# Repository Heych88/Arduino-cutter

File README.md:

# Arduino-cutter
Arduino controller implementation of a plastic or resistor cutter.

The controller daughter board contains the follow external board connections;

 * 6 -> 14v
 * Four push-buttons
 * Adjustable potentiometer
 * E-stops
 * 4-bit LCD
 * Single pulse encoder
 * Two solenoid relays, active low, 5v or Vin
 * Stepper motor, 2A
 * Fuse connector

## Hardware Setup

The parts required and the daughterboard PCB Gerber files are located in the EagleBoard folder.

The interfacing of the components is as follows.

## Installing

1. Clone this repository

 ```sh
 git clone https://github.com/Heych88/Arduino-cutter.git
 ```

2. Download Arduino IDE from [here](https://www.arduino.cc/en/Main/Software).

3. If you are installing a brand-new Arduino Leonardo board, the EEPROM must be flashed first. If it is the existing system board, continue from step 4.

 1. Load the `eeprom_write.ino` file, located in the `/src/eeprom_write/` folders, into the Arduino IDE.

 2. Compile and load the file onto the Arduino board.

4. Load any of the `.ino` files, located in the `/src/` folders, into the Arduino IDE.

5. Compile and load the files onto the Arduino board.

Detailed programming and system information can be found in the *Arduino Cutter Instructions* document, located in the `/documents/` folder.

## Usage

This repository provides a daughterboard and usable code to run an Arduino plastic or resistor cutter.

## Contributing

1. Fork it!
2. Create your feature branch: `git checkout -b my-new-feature`
3. Commit your changes: `git commit -am 'Add some feature'`
4. Push to the branch: `git push origin my-new-feature`
5. Submit a pull request :D

## License

This project is licensed under the GNU-GPL3 License - see the [LICENSE.md](LICENSE.md) file for details.

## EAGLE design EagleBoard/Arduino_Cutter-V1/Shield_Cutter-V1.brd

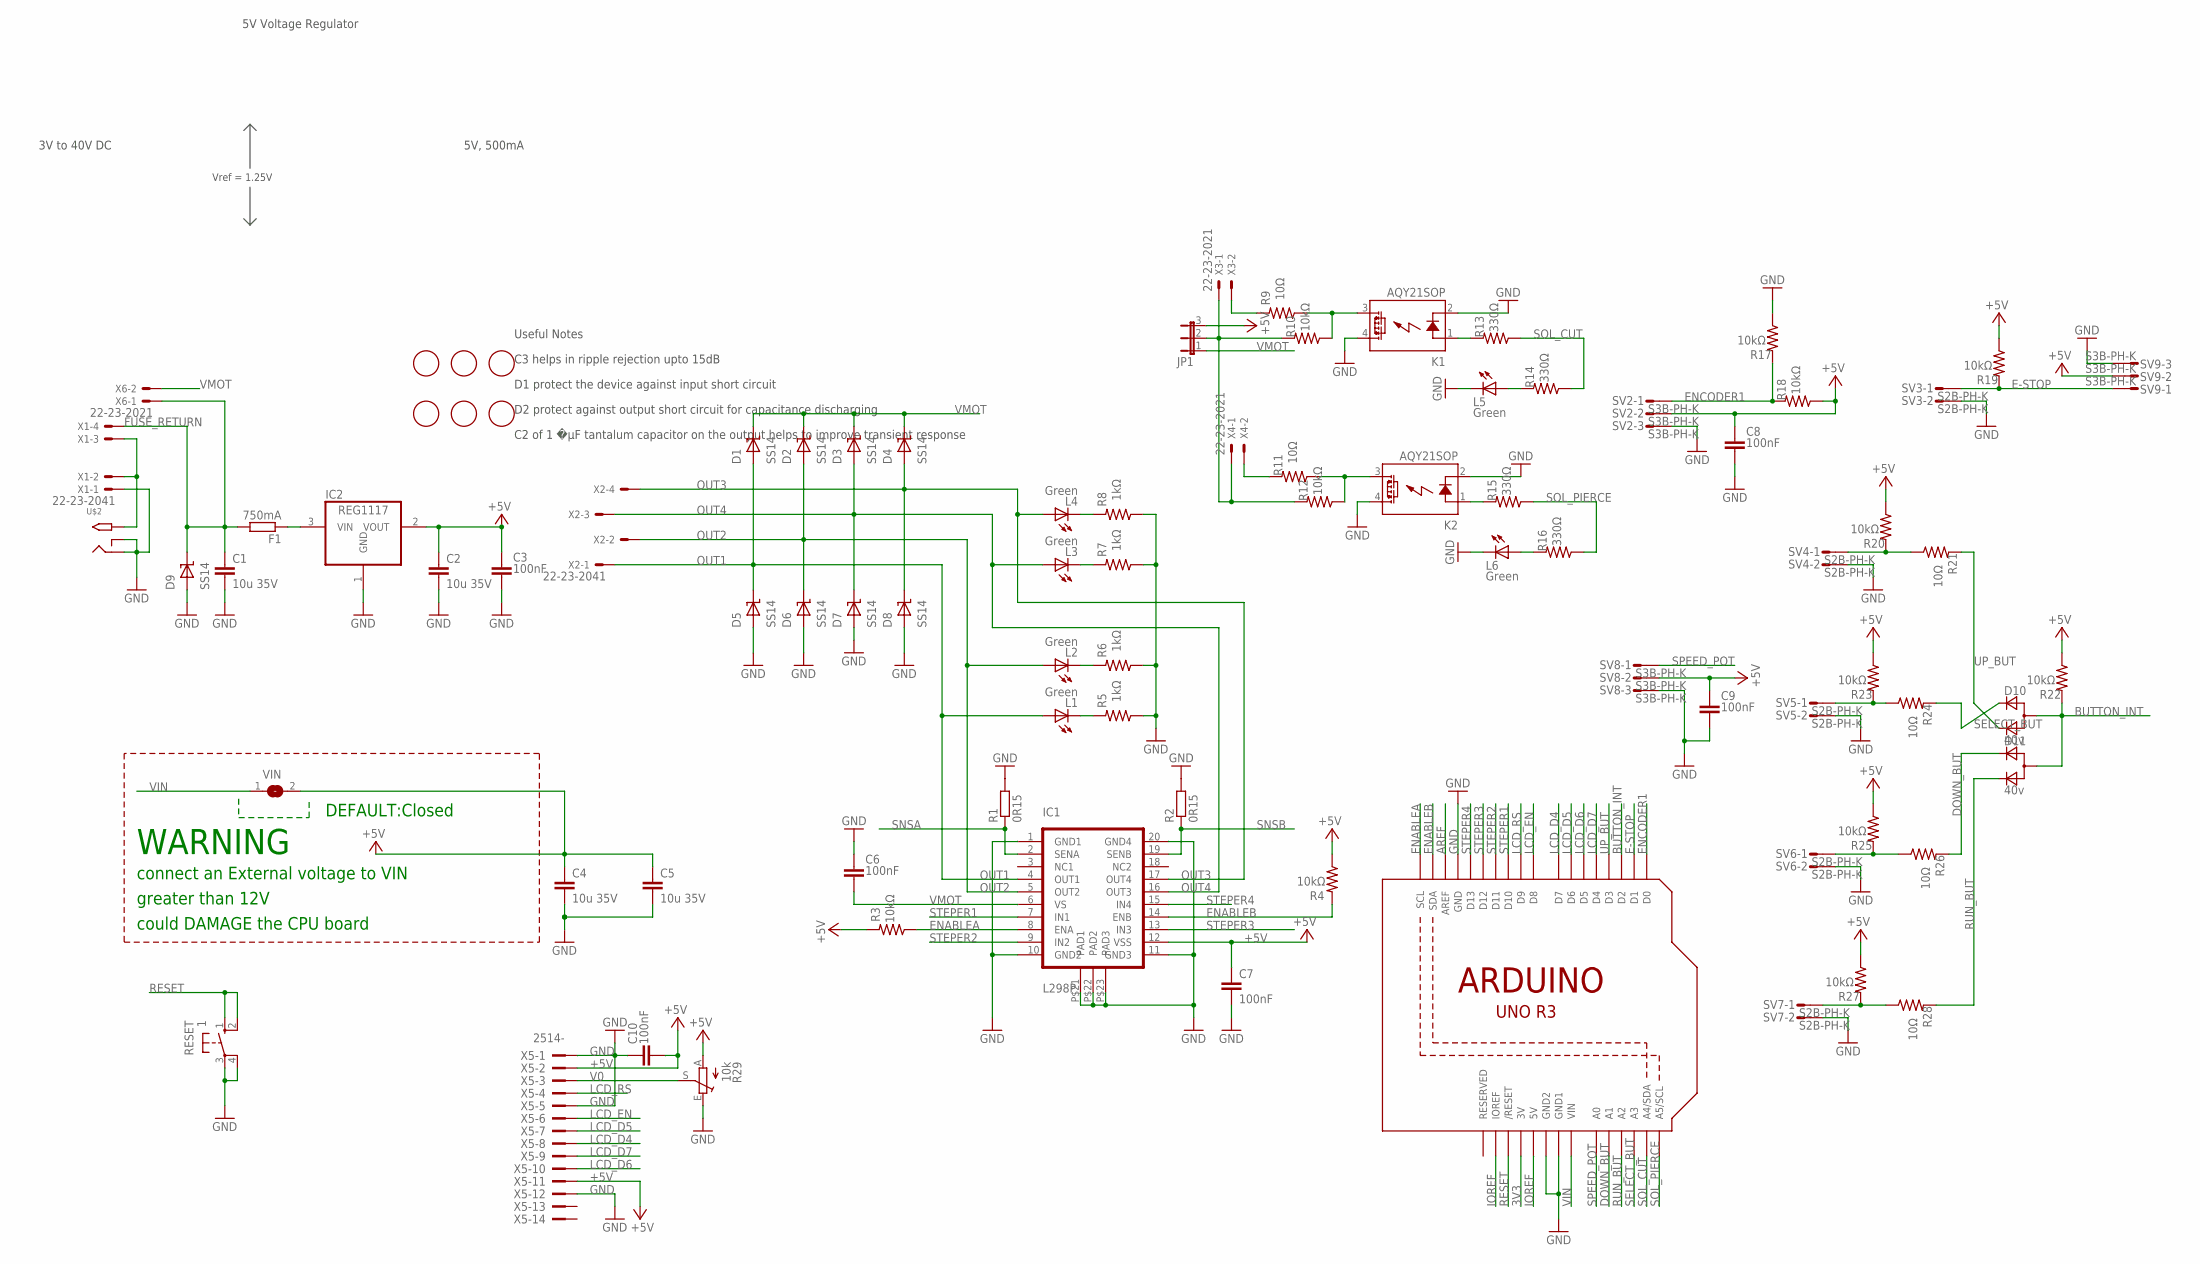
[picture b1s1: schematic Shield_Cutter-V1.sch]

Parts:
C1, C2, C4, C5: 10u 35V; C1210
C3, C6, C7, C8, C9, C10: 100nF; C0805
D1, D2, D3, D4, D5, D6, D7, D8, D9: SS14; SMA
D10, D11: 40v; SOT323
F1: 750mA; R1206
FID1, FID2, FID3, FID4, FID5, FID6: FIDUCIALMOUNT; FIDUCIA-MOUNT
IC1: L298P; POWER-SO20
IC2: REG1117; SOT223
JP1: JP2E; JP2
K1, K2: AQY21SOP; SOP04
L1, L2, L3, L4, L5, L6: Green; CHIPLED_0805
R1, R2: 0R15; R1206
R3, R4, R10, R12, R17, R18, R19, R20, R23, R25, R27: 10kΩ; R0805
R5, R6, R7, R8: 1kΩ; R0805
R9, R11, R21, R24, R26, R28: 10Ω; R0805
R13, R14, R15, R16: 330Ω; R0805
R22: 10kΩ; M0805
R29: 10k; S64W
RESET: 1; B3F-10XX
SV2, SV8, SV9: S3B-PH-K; S03P
SV3, SV4, SV5, SV6, SV7: S2B-PH-K; S02P
U1: ARDUINOR3-DIMENSION; ARDUINOR3
U$2: 2.1MMJACKTHM; PJ-102A
VIN: SJW
X1, X2: 22-23-2041
X3, X4, X6: 22-23-2021
X5: 2514-; PAK100/2500-14

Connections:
3V3: U1.3V
+5V: C2.1, C3.1, C4.1, C5.1, C7.1, C8.1, C9.1, C10.2, IC1.P$12 (VSS), IC2.2 (VOUT), JP1.3, R3.2, R4.1, R18.1, R19.1, R20.1, R22.1, R23.1, R25.1, R27.1, R29.A, SV2.2, SV8.2, SV9.2, VIN.2, X5.2, X5.11
AREF: U1.AREF
BUTTON_INT: D10.1 (A), D11.1 (A), R22.2, U1.D2
DOWN_BUT: D11.2 (C1), R26.2, U1.A1
E-STOP: R19.2, SV3.1, SV9.1, U1.D1
ENABLEA: IC1.P$8 (ENA), R3.1, U1.SCL
ENABLEB: IC1.P$14 (ENB), R4.2, U1.SDA
ENCODER1: R17.2, R18.2, SV2.1, U1.D0
FUSE_RETURN: C1.1, D9.P$1 (K), F1.2, X1.4, X6.1
GND: C1.2, C2.2, C3.2, C4.2, C5.2, C6.1, C7.2, C8.2, C9.2, C10.1, D5.P$2 (A), D6.P$2 (A), D7.P$2 (A), D8.P$2 (A), D9.P$2 (A), IC1.P$1 (GND1), IC1.P$10 (GND2), IC1.P$11 (GND3), IC1.P$20 (GND4), IC1.P$21 (PAD1), IC1.P$22 (PAD2), IC1.P$23 (PAD3), IC2.1 (GND), K1.2 (K), K1.4 (DS1), K2.2 (K), K2.4 (DS1), L5.C, L6.C, R1.2, R2.2, R5.1, R6.1, R7.1, R8.1, R17.1, R29.E, RESET.3, RESET.4 (P1), SV2.3, SV3.2, SV4.2, SV5.2, SV6.2, SV7.2, SV8.3, SV9.3, U1.GND, U1.GND1, U1.GND2, U$2.RING, U$2.RING_SW, X1.1, X5.1, X5.5, X5.12
IOREF: U1.5V, U1.IOREF
LCD_D4: U1.D7, X5.8
LCD_D5: U1.D6, X5.7
LCD_D6: U1.D5, X5.10
LCD_D7: U1.D4, X5.9
LCD_EN: U1.D8, X5.6
LCD_RS: U1.D9, X5.4
unnamed: L4.C, R8.2
unnamed: L3.C, R7.2
unnamed: L2.C, R6.2
unnamed: L1.C, R5.2
unnamed: K1.1 (A), R13.2
unnamed: L5.A, R14.2
unnamed: R9.2, X3.2
unnamed: R23.2, R24.1, SV5.1
unnamed: JP1.2, R10.2, R12.2, X3.1, X4.1
unnamed: K2.3 (DS2), R11.1, R12.1
unnamed: L6.A, R16.2
unnamed: R20.2, R21.1, SV4.1
unnamed: K2.1 (A), R15.2
unnamed: R11.2, X4.2
unnamed: K1.3 (DS2), R9.1, R10.1
unnamed: R25.2, R26.1, SV6.1
unnamed: F1.1, IC2.3 (VIN)
unnamed: R27.2, R28.1, SV7.1
OUT1: D1.P$2 (A), D5.P$1 (K), IC1.P$4 (OUT1), L1.A, X2.1
OUT2: D2.P$2 (A), D6.P$1 (K), IC1.P$5 (OUT2), L2.A, X2.2
OUT3: D4.P$2 (A), D8.P$1 (K), IC1.P$17 (OUT4), L4.A, X2.4
OUT4: D3.P$2 (A), D7.P$1 (K), IC1.P$16 (OUT3), L3.A, X2.3
POWERIN: U$2.TIP, X1.2, X1.3
RESET: RESET.1 (S), RESET.2 (S1), U1.RESET (/RESET)
RUN_BUT: D11.3 (C2), R28.2, U1.A2
SELECT_BUT: D10.2 (C1), R24.2, U1.A3
SNSA: IC1.P$2 (SENA), R1.1
SNSB: IC1.P$19 (SENB), R2.1
SOL_CUT: R13.1, R14.1, U1.A4 (A4/SDA)
SOL_PIERCE: R15.1, R16.1, U1.A5 (A5/SCL)
SPEED_POT: SV8.1, U1.A0
STEPER1: IC1.P$7 (IN1), U1.D10
STEPER2: IC1.P$9 (IN2), U1.D11
STEPER3: IC1.P$13 (IN3), U1.D12
STEPER4: IC1.P$15 (IN4), U1.D13
UP_BUT: D10.3 (C2), R21.2, U1.D3
V0: R29.S, X5.3
VIN: U1.VIN, VIN.1
VMOT: C6.2, D1.P$1 (K), D2.P$1 (K), D3.P$1 (K), D4.P$1 (K), IC1.P$6 (VS), JP1.1, X6.2

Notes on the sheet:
WARNING
connect an External voltage to VIN
greater than 12V
could DAMAGE the CPU board
DEFAULT:Closed
5V Voltage Regulator
C3 helps in ripple rejection upto 15dB
D1 protect the device against input short circuit
D2 protect against output short circuit for capacitance discharging
C2 of 1 �µF tantalum capacitor on the output helps to improve transient response
Useful Notes
5V, 500mA
3V to 40V DC
Vref = 1.25V

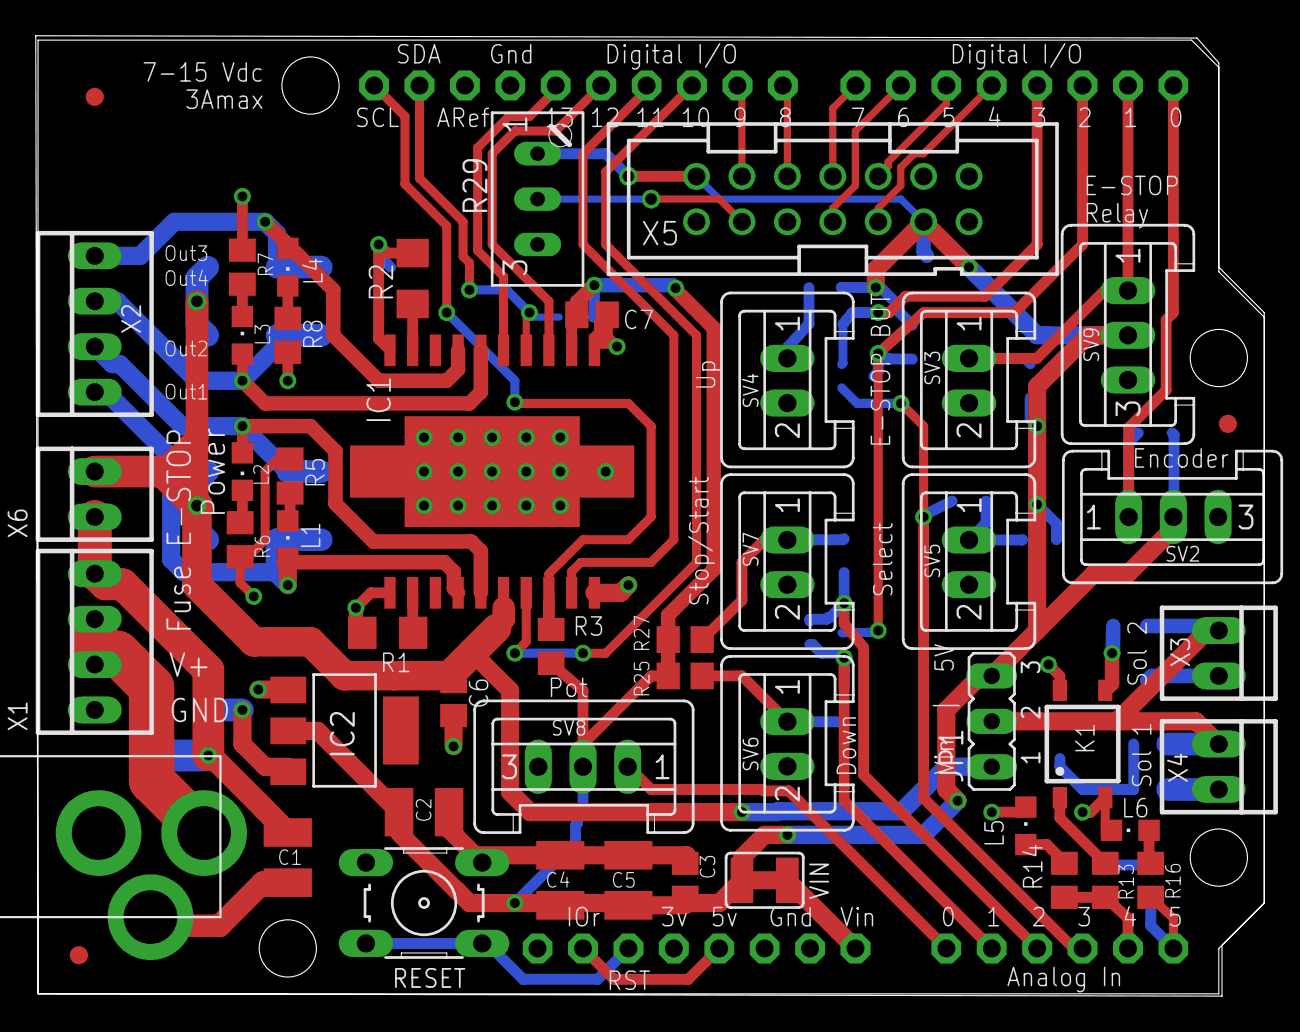
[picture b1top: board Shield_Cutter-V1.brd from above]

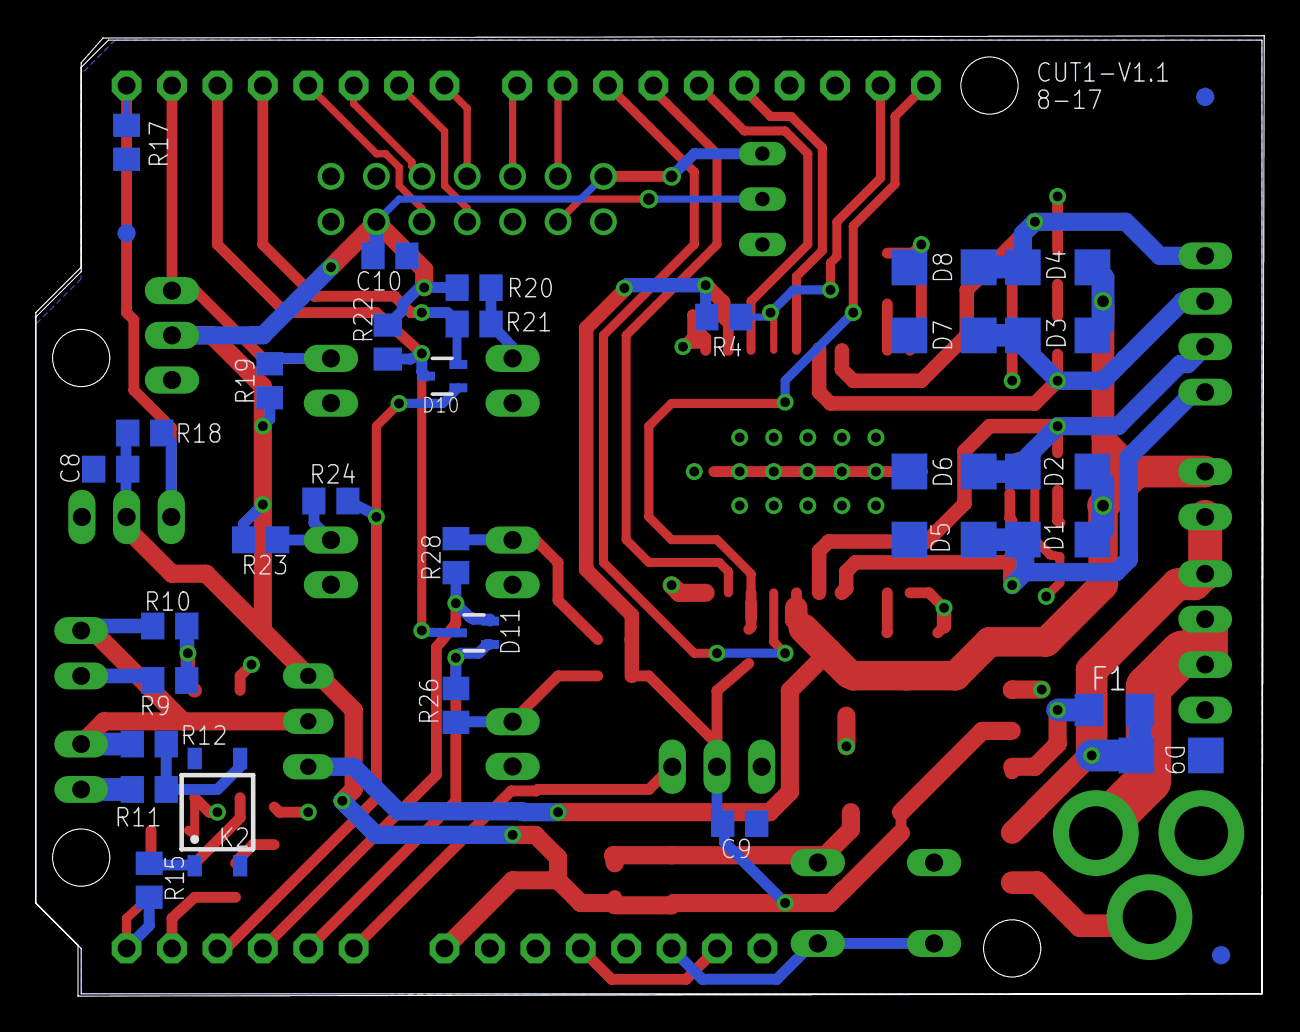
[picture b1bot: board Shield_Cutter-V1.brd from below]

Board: 2 copper layers, 68.7 x 53.7 mm, 86 parts (35 on the bottom side), 55 nets.

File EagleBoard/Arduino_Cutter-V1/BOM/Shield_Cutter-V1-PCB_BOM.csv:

Qty,Value,MPN,Digi-key,Package,Parts,Description
1,,61300311121,732-5316-ND,JP2,JP1,CONN HEADER 3 POS 2.54
2,0R15,RL1206FR-7W0R15L,311-.15LYCT-ND,R1206,"R1, R2",RES SMD 0.15 OHM 1% 1/2W 1206
1,,B3F-1002,SW401-ND,B3F-10XX,RESET,SWITCH TACTILE SPST-NO 0.05A 24V
6,100nF,C0805C104K5RACTU,399-1170-1-ND,C0805,"C3, C6, C7, C8, C9, C10",0.1µF ±10% 50V Ceramic Capacitor X7R 0805 (2012 Metric)
1,10k,PV36W103C01B00,490-2875-ND,S64W,R29,POTENTIOMETER
12,10kΩ,RMCF0805FT10K0,RMCF0805FT10K0CT-ND,R0805,"R3, R4, R10, R12, R17, R18, R19, R20, R22, R23, R25, R27","±1% 0.125W, 1/8W Chip Resistor 0805 (2012 Metric) "
4,10u 35V,C1210C106K3RACTU,399-8224-1-ND,C1210,"C1, C2, C4, C5","CAPACITOR, European symbol"
6,10Ω,RC0805FR-0710RL,RMCF0805FT10R0CT-ND,R0805,"R9, R11, R21, R24, R26, R28",RES SMD 10 OHM 1% 1/8W 0805
4,1kΩ,RMCF0805FT1K00,RMCF0805FT1K00CT-ND,R0805,"R5, R6, R7, R8","±1% 0.125W, 1/8W Chip Resistor 0805 (2012 Metric)"
3,22-23-2021,OSTVN02A150,ED10561-ND,22-23-2021,"X1, X4, X5",".100"" (2.54mm) Center Header - 2 Pin"
1,22-23-2041,OSTVN04A150,ED10563-ND,22-23-2041,X2,CONN TERM BLOCK 2.54MM 4POS PCB
1,2514-,302-S141,ED10522-ND,PAK100/2500-14,X5,"14 Positions Header Connector 0.100"" (2.54mm) Through Hole"
4,330Ω,RMCF0805FT330R,RMCF0805FT330RCT-ND,R0805,"R13, R14, R15, R16","±1% 0.125W, 1/8W Chip Resistor 0805 (2012 Metric)"
2,40v,"BAT54AW,115",1727-3567-1-ND,SOT323,"D10, D11","Diode Array 1 Pair Common Anode Schottky 200mA (DC) Surface Mount SC-70, SOT-323"
2,AQY21SOP,CPC1020NTR,CLA318CT-ND,SOP04,"K1, K2",PhotoMOS Relay NAiS
6,Green,LG R971-KN-1,475-1410-1-ND,CHIPLED_0805,"L1, L2, L3, L4, L5, L6",LED GREEN DIFFUSED 0805 SMD
1,L298P,L298P,497-1396-5-ND,POWER-SO20,IC1,L298P DUAL FUL-BRIDGE DRIVER PowerSO20
1,REG1117,REG1117-5/2K5,296-27924-1-ND,SOT223,IC2,800mA and 1A Low Dropout (LDO) Positive Regulator
6,S2B-PH-K,B2B-XH-A(LF)(SN),455-2247-ND,S02P,"SV1, SV3, SV4, SV5, SV6, SV7",CONN HEADER XH TOP 2POS 2.5MM
3,S3B-PH-K,B3B-XH-A(LF)(SN),455-2248-ND,S03P,"SV2, SV8, SV9",CONN HEADER XH TOP 3POS 2.5MM
9,SS14,MBRAF360T3G,MBRAF360T3GOSCT-ND,SMA,"D1, D2, D3, D4, D5, D6, D7, D8, D9",DIODE SCHOTTKY 60V 4A SMA

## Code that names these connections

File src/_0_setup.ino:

#include <LiquidCrystal.h>
#include <Stepper.h>

/******************************** Push Buttons & E-Stop *******************************/
#define E_STOP_BUT 1
#define BUTTON_INTERRUPT 2
#define SELECT_BUT A3
#define UP_BUT 3
#define DOWN_BUT A1
#define START_BUT A2

volatile bool e_stop_active = false;

/*************************************** LCD *****************************************/
// initialize the library with the numbers of the interface pins
LiquidCrystal lcd(9,8,6,7,4,5);

#define DISPLAY_ROWS 2
#define DISPLAY_COLS 16

char blank_line[DISPLAY_COLS];

/************************************ Solenoids **************************************/
#define SOLENOID_CUT A4
#define SOLENOID_PIERCE A5

/************************************ Solenoids **************************************/
#define TRIM_POT A0

/*************************************************************************************/

void setup() {

  // init motor parameters
  pinMode(SDA, OUTPUT);
  digitalWrite(SDA, LOW); // disable motor

  // init push buttons
  pinMode(SELECT_BUT, INPUT_PULLUP);
  pinMode(UP_BUT, INPUT_PULLUP);
  pinMode(DOWN_BUT, INPUT_PULLUP);
  pinMode(START_BUT, INPUT_PULLUP);
  pinMode(BUTTON_INTERRUPT, OUTPUT);

  // init solenoid parameters
  pinMode(SOLENOID_CUT, OUTPUT);
  pinMode(SOLENOID_PIERCE, OUTPUT);

  // set the E-stop button pin as an intterupt
  delay(500);
  pinMode(E_STOP_BUT, INPUT_PULLUP);
  attachInterrupt(digitalPinToInterrupt(E_STOP_BUT), intEStop, CHANGE);

  // set up the LCD's number of columns and rows:
  lcd.begin(DISPLAY_COLS, DISPLAY_ROWS);

  // create a blank string for clearing the text on one row of the LCD display
  for (int i=0; i < DISPLAY_COLS; i++) {
    blank_line[i] = ' ';
  }

  // check if E-stop is active
  if (digitalRead(E_STOP_BUT) == HIGH) e_stop_active = true;
}

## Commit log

2017-07-28 init commit
2017-07-28 add motor control
2017-07-31 Feat: add E-stop intterrupt to system
2017-07-31 Feat: add stop/start button and E-Stop polling
2017-07-31 Feat: add menus and menu scroll
2017-08-02 Feat: add speed adjust and pushbutton capture
2017-08-02 Feat: add quantity menu and adjustment
2017-08-02 Feat: add cut length menu and adjustment
2017-08-03 Feat: add blinking cursor on menu select
2017-08-05 Feat: add pcb board
2017-08-06 Feat: pcb routed
2017-08-06 Feat: add pcb ground plane
2017-08-06 Feat: add text on silk screen
2017-08-06 Feat: init gerber files
2017-08-07 FIX: increase components to 0805 size
2017-08-07 Chore: gerbers and files for pcb manufacture
2017-08-08 Chore: add part names to pcb and cap from vmot to ground
2017-08-08 chore: init BOM's
2017-08-27 chore: update BOM
2017-08-31 Chore: add License
2017-09-12 Fix: fix floating ground. Feat: add power input terminal.
2017-09-17 Feat: add fuse to 5v power
2017-09-17 chore: change LCD pinouts
2017-09-21 chore: update E-STOP to new board
2017-09-21 chore: update push-buttons to new board
2017-09-21 feat: add stepper motor to new board
2017-10-23 Fix: stepper motor stop and overheat
2017-10-26 Feat: push button interrupt enabled
2017-10-30 Fix: motor overheat minimise
2017-10-30 Feat: add solenoid
2017-11-06 Feat: add button features
2017-11-06 Feat: add display
2017-11-06 Feat: add solenoids
2017-11-06 Feat: add pierce menus
2017-11-06 Feat: creates one sleeve
2017-11-06 Feat: single select press only
2017-11-13 Feat: values update in a single function
2017-11-13 chore: remove unused code
2017-11-13 change: min/max clip function
2017-11-13 Feat: clear current qty
2017-11-14 Feat: adjustable solenoid delay
2017-11-15 feat: add trim pot for speed
2017-11-15 fix: speed at zero stops all
2017-11-15 Change: pierce distance min/max
2017-11-15 Fix: motor run after speed is zero
2017-11-15 Fix: qty count on speed stop
2017-11-16 feat: converts distance into counts
2017-11-16 fix: distance steps change: move motor prams to motor file
2017-12-07 Fix: steps for each length maths
2017-12-07 Feat: add adjustable steps per stepper motor revolution
2017-12-08 Feat: add adjustable drive wheel diameter
2017-12-08 Chore: Update comments
2017-12-08 Change: move stepper class into drive loop
2017-12-08 Chore: change unused returns to void
2017-12-08 Chore: rename files for eeprom
2017-12-08 Feat: add EEPROM write and read
2017-12-08 Feat: define addresses
2017-12-08 Feat: writes to eeprom after value updates
2017-12-12 Feat: Add units on to displayed values
2017-12-12 Feat: Remove serial to prevent lockup
2017-12-13 Feat: add pierce solenoid offset from cut solenoid
2017-12-13 Chore: Add instruction documentation
2017-12-15 chore: Update
2017-12-15 Chore: add README
